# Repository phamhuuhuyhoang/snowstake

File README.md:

# SnowStake

### Overview

This guide is to use a photon development board to track inches of snow in the mountain and show it with illuminated LEDs

### Getting started

- install npm
- npm install
- install visual studio community
- add the USB from the visual studio installer
- run 'particle setup'

### Resources

- [Photon Dev link](https://docs.particle.io/photon/)
- [particle CLI windows](https://docs.particle.io/tutorials/developer-tools/cli/#using-windows)

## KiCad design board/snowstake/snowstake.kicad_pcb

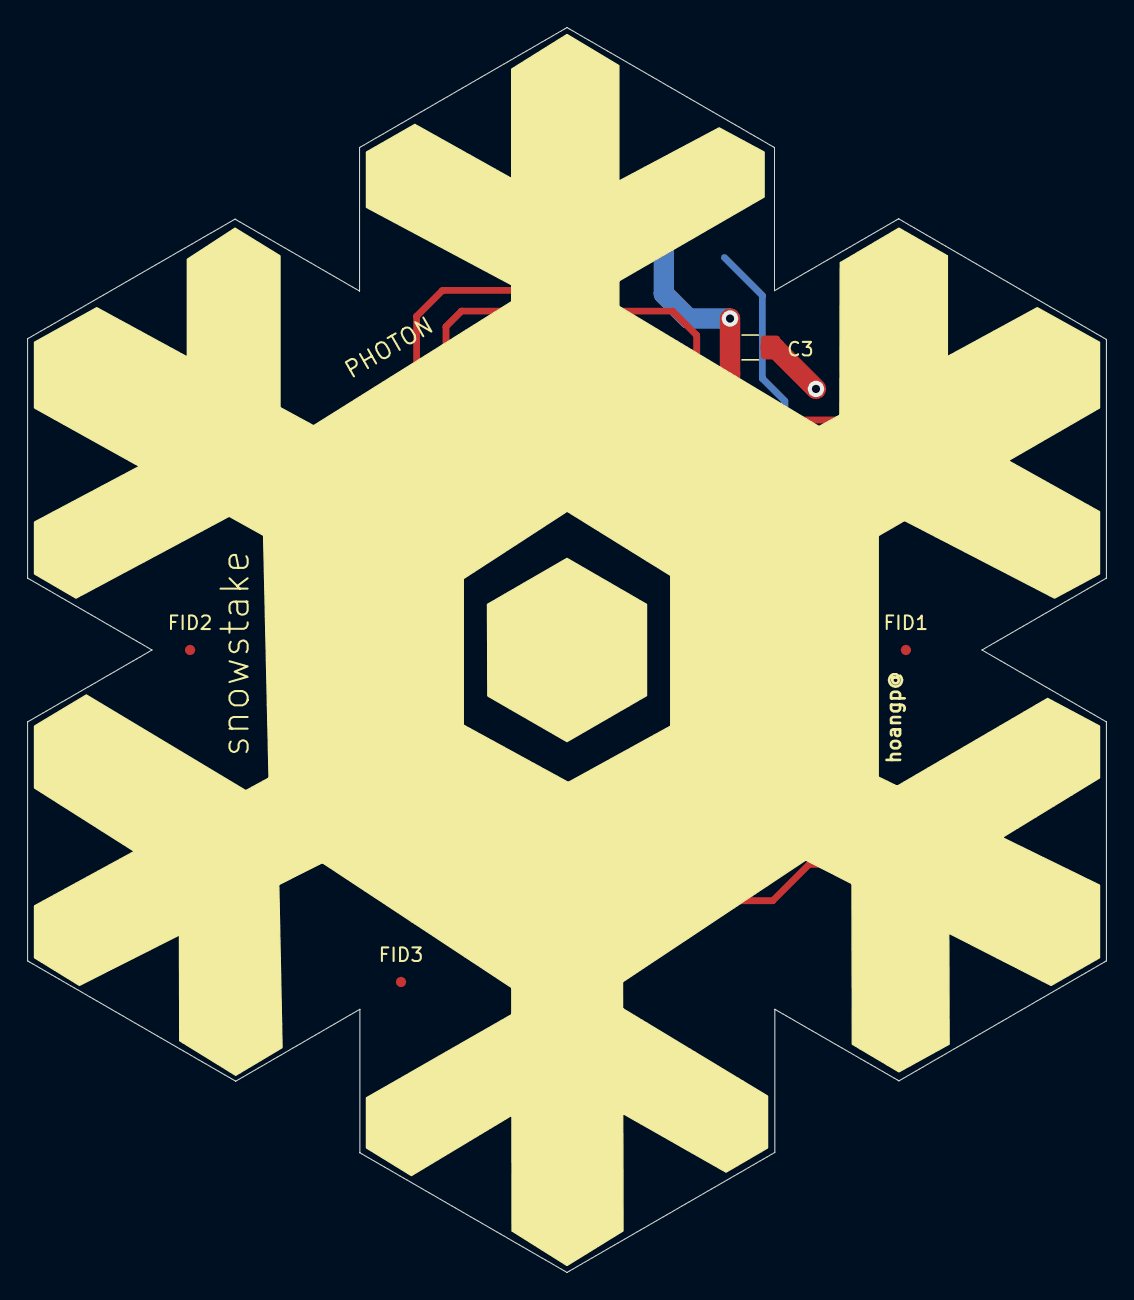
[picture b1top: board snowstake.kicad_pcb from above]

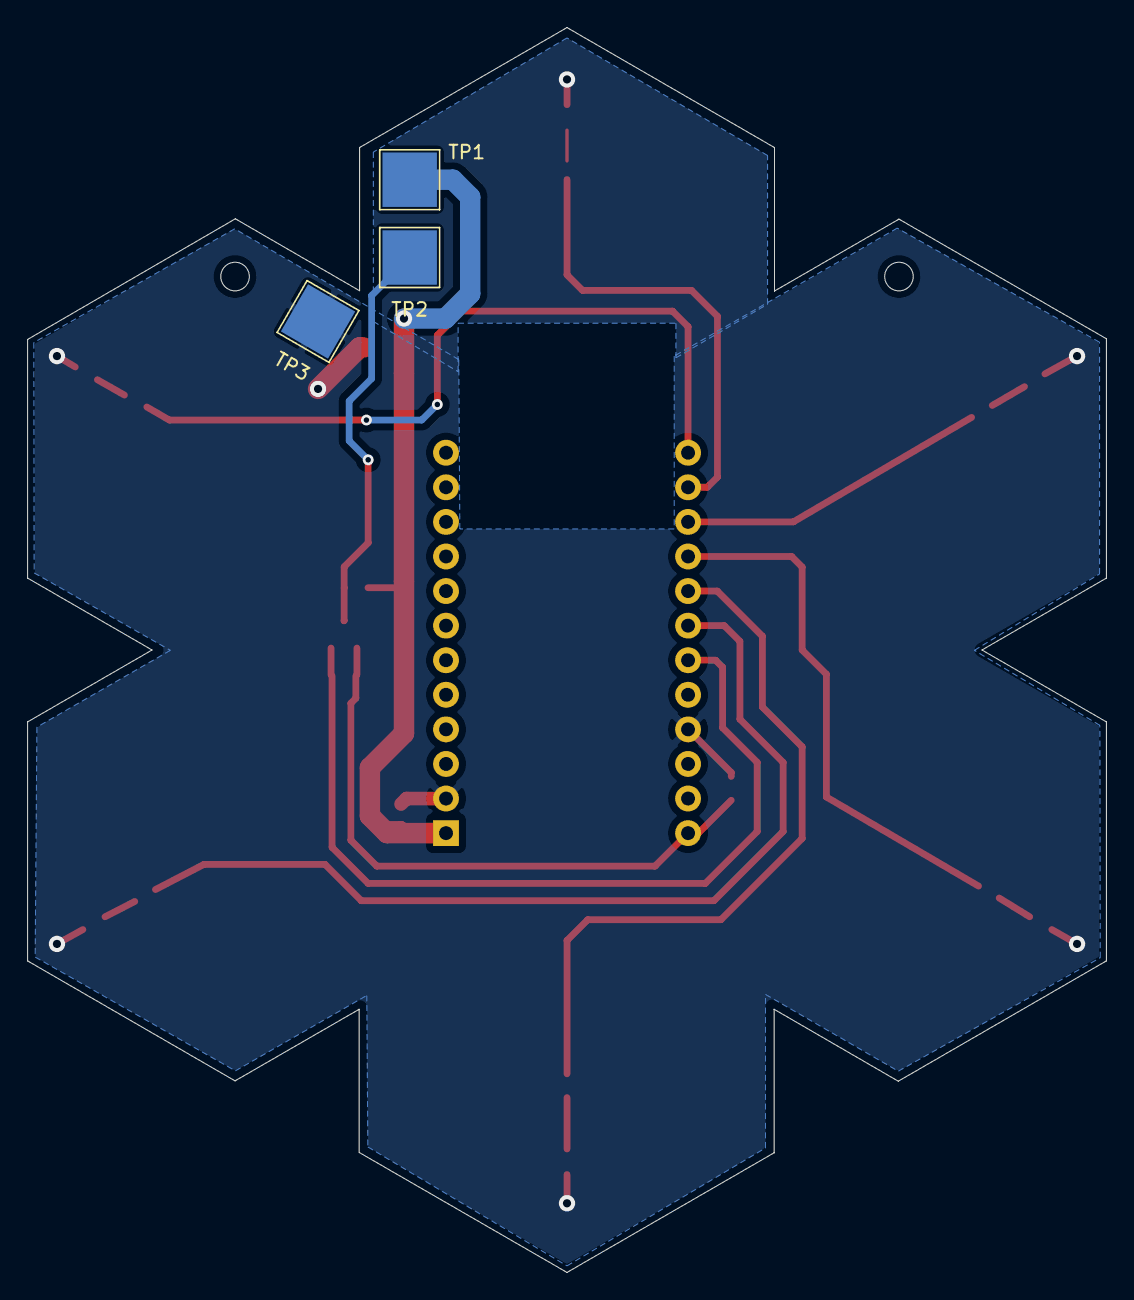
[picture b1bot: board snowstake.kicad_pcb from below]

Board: 2 copper layers, 79.2 x 91.4 mm, 27 parts (3 on the bottom side), 17 nets.

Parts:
C1, C2: C; R_0603_1608Metric_Pad1.05x0.95mm_HandSolder
C3: C; R_1206_3216Metric_Pad1.42x1.75mm_HandSolder
D1, D2, D3, D4, D5, D6: LED; LED_0805_2012Metric
FID1, FID2, FID3: Fiducial; Fiducial_0.75mm_Mask1.5mm
H1, H2: MountingHole; MountingHole_2.1mm
Q2: BSS138; SOT-23
R2, R3, R4, R5, R7, R8: 499; R_0603_1608Metric_Pad1.05x0.95mm_HandSolder
R6, R9: 4.99k; R_0603_1608Metric_Pad1.05x0.95mm_HandSolder
TP1, TP2, TP3: TestPoint; TestPoint_Pad_4.0x4.0mm
U1: PHOTON; photon_tht

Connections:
+3V3: C2.2, Q2.1, R6.1, U1.24
+5V: C1.1, C3.1, R9.1, TP1.1, U1.1
/D0: R2.1, U1.13
/D1: R3.1, U1.14
/D2: R4.1, U1.15
/D3: R5.1, U1.16
/D4: R7.1, U1.17
/D5: R8.1, U1.18
/D6: Q2.2, R6.2, U1.19
/DIN: Q2.3, R9.2, TP2.1
GND: C1.2, C2.1, C3.2, D1.1, D2.1, D3.1, D4.1, D5.1, D6.1, TP3.1, U1.2, U1.21
unnamed: D1.2, R2.2
unnamed: D2.2, R3.2
unnamed: D3.2, R4.2
unnamed: D4.2, R5.2
unnamed: D5.2, R7.2
unnamed: D6.2, R8.2

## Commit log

2021-05-06 Updated schematic and layout
    Added 6 LED for each corner in schematic
    Started placing component
2021-05-14 added mounting hole and fiducial
    added mounting holes and fiducials to schematic and import to layout
2021-05-30 Updated geometry and generated gerbers
    Corrected board geometry to use mathematical angles for hexagon instead of just eye balling it. Generated gerber fabrication files.
2021-05-30 separated LED control and changed routing
    on board LED now have independent control with individual GPIO. Layout updated to clean up routing
2021-05-30 Added BOM and pick place
    Generated BOM and pick place file
2021-10-20 commint first dev changes.
2021-10-22 Adding working ESP8266 code
2021-10-22 Added Secrets files, added Photon code, Added ESP8266 code
2021-10-25 Changing Weather logic, and inserting snow where it belongs.
2021-11-28 adding esp32 support and new ui
